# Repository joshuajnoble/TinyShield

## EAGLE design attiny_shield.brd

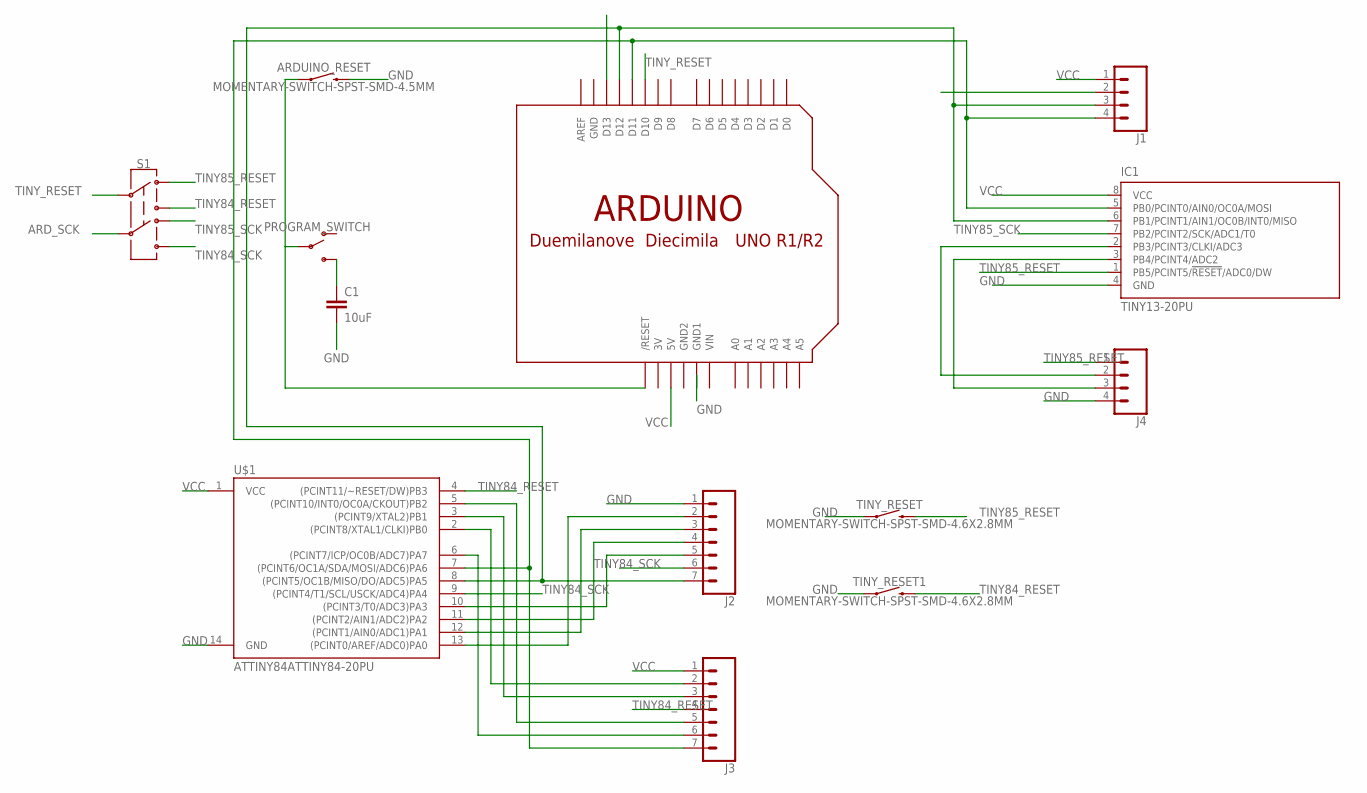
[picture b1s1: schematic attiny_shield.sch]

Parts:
ARDUINO_RESET: MOMENTARY-SWITCH-SPST-SMD-4.5MM; TACTILE_SWITCH_SMD_4.5MM
C1: 10uF; 0805
IC1: TINY13-20PU; DIL08
J1, J4: CONN_04; 1X04
J2, J3: CONN_07; 1X07
PROGRAM_SWITCH: SWITCH-SPDT-SMD-AYZ0202; SWITCH_DPDT_SMD_AYZ0202
S1: SWITCH-DPDT-SMD-AYZ0202; SWITCH_DPDT_SMD_AYZ0202
TINY_RESET, TINY_RESET1: MOMENTARY-SWITCH-SPST-SMD-4.6X2.8MM; TACTILE_SWITCH_SMD_4.6X2.8MM
U$1: ATTINY84ATTINY84-20PU; DIP14
U$2: ARDUINO-NODIM

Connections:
3V: U$2.3V
84_0: J2.2, U$1.13 ((PCINT0/AREF/ADC0)PA0)
84_1: J2.3, U$1.12 ((PCINT1/AIN0/ADC1)PA1)
84_5: IC1.6 (PB1/PCINT1/AIN1/OC0B/INT0/MISO), J1.3, J2.7, U$1.8 ((PCINT5/OC1B/MISO/DO/ADC5)PA5), U$2.D12
84_6: IC1.5 (PB0/PCINT0/AIN0/OC0A/MOSI), J1.4, J3.7, U$1.7 ((PCINT6/OC1A/SDA/MOSI/ADC6)PA6), U$2.D11
ARD_SCK: S1.5, U$2.D13
GND: ARDUINO_RESET.1 (2), ARDUINO_RESET.4 (2), C1.2, IC1.4 (GND), J2.1, J4.4, TINY_RESET.1, TINY_RESET.2 (1), TINY_RESET1.1, TINY_RESET1.2 (1), U$1.14 (GND), U$2.GND
GND1: U$2.GND1
GND2: U$2.GND2
unnamed: IC1.2 (PB3/PCINT3/CLKI/ADC3), J4.2
unnamed: IC1.3 (PB4/PCINT4/ADC2), J4.3
unnamed: C1.1, PROGRAM_SWITCH.3 (S)
unnamed: ARDUINO_RESET.2 (1), ARDUINO_RESET.3 (1), PROGRAM_SWITCH.2, U$2.RESET (/RESET)
unnamed: J2.4, U$1.11 ((PCINT2/AIN1/ADC2)PA2)
unnamed: J2.5, U$1.10 ((PCINT3/T0/ADC3)PA3)
unnamed: J3.6, U$1.6 ((PCINT7/ICP/OC0B/ADC7)PA7)
unnamed: J3.2, U$1.2 ((PCINT8/XTAL1/CLKI)PB0)
unnamed: J3.3, U$1.3 ((PCINT9/XTAL2)PB1)
unnamed: J3.5, U$1.5 ((PCINT10/INT0/OC0A/CKOUT)PB2)
TINY84_RESET: J3.4, S1.3, TINY_RESET1.3 (2), TINY_RESET1.4 (2), U$1.4 ((PCINT11/~RESET/DW)PB3)
TINY84_SCK: J2.6, S1.6, U$1.9 ((PCINT4/T1/SCL/USCK/ADC4)PA4)
TINY85_RESET: IC1.1 (PB5/PCINT5/!RESET!/ADC0/DW), J4.1, S1.1, TINY_RESET.3 (2), TINY_RESET.4 (2)
TINY85_SCK: IC1.7 (PB2/PCINT2/SCK/ADC1/T0), J1.2, S1.4
TINY_RESET: S1.2, U$2.D10
VCC: IC1.8 (VCC), J1.1, J3.1, U$1.1 (VCC), U$2.5V
VIN: U$2.VIN

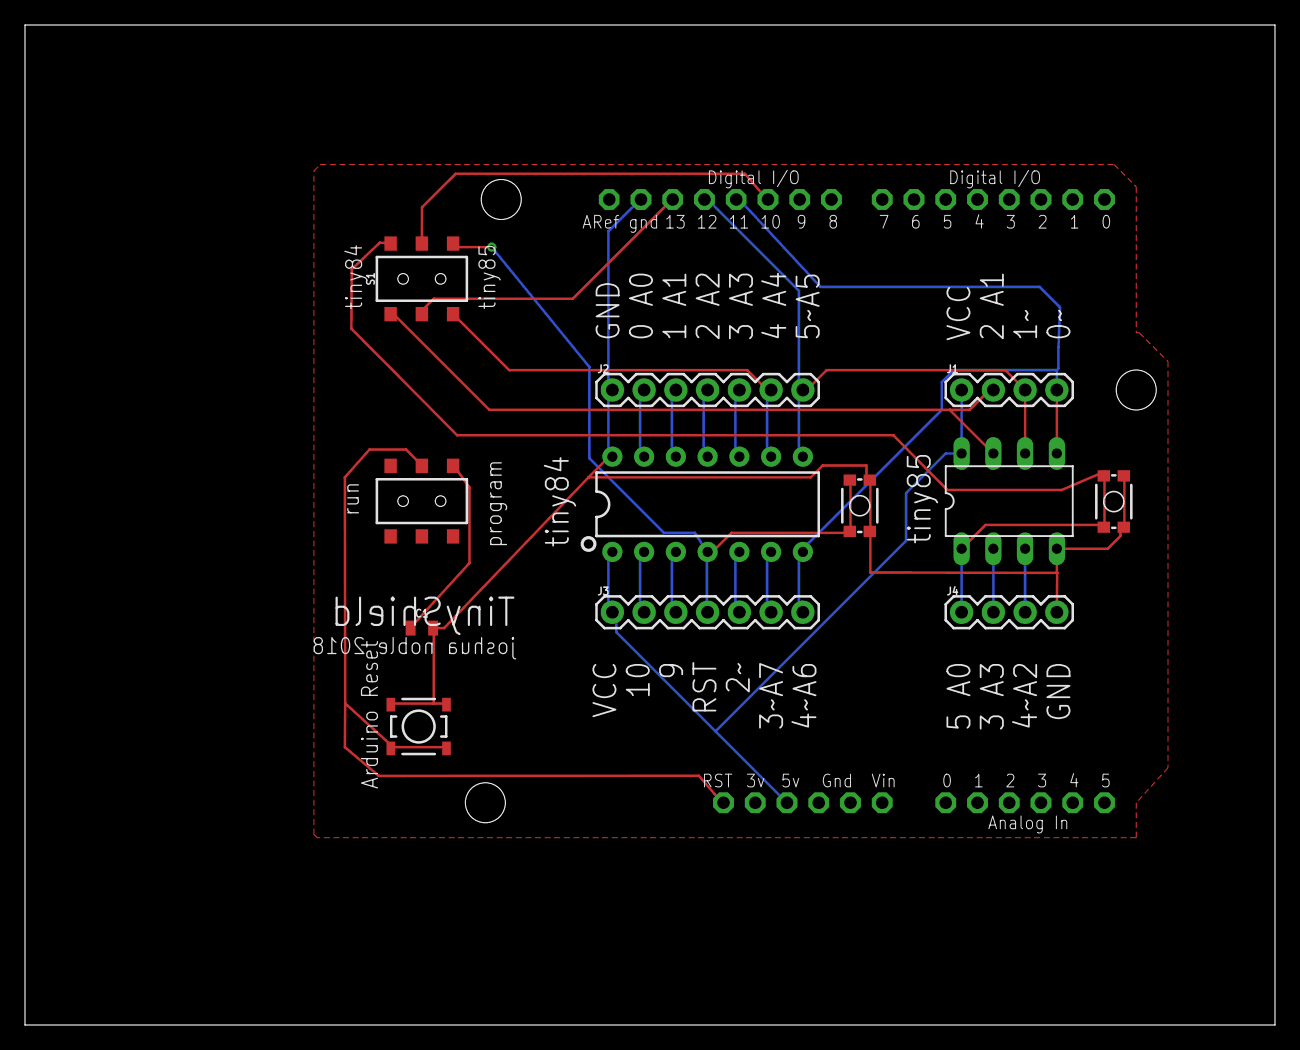
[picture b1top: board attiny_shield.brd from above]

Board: 2 copper layers, 100.0 x 80.0 mm, 13 parts (0 on the bottom side), 22 nets.

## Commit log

2018-02-11 named
2018-02-12 reset pins won't need to be set manually
2018-02-12 updating gitignore
2018-02-12 working gitignore
2018-02-12 reset not vcc
2018-02-12 pours
2018-02-12 added reset switch
2018-02-12 independent resets

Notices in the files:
parts and their libraries:
SparkFun-Switches: Licensing: Creative Commons ShareAlike 4.0 International - https://creativecommons.org/licenses/by-sa/4.0
